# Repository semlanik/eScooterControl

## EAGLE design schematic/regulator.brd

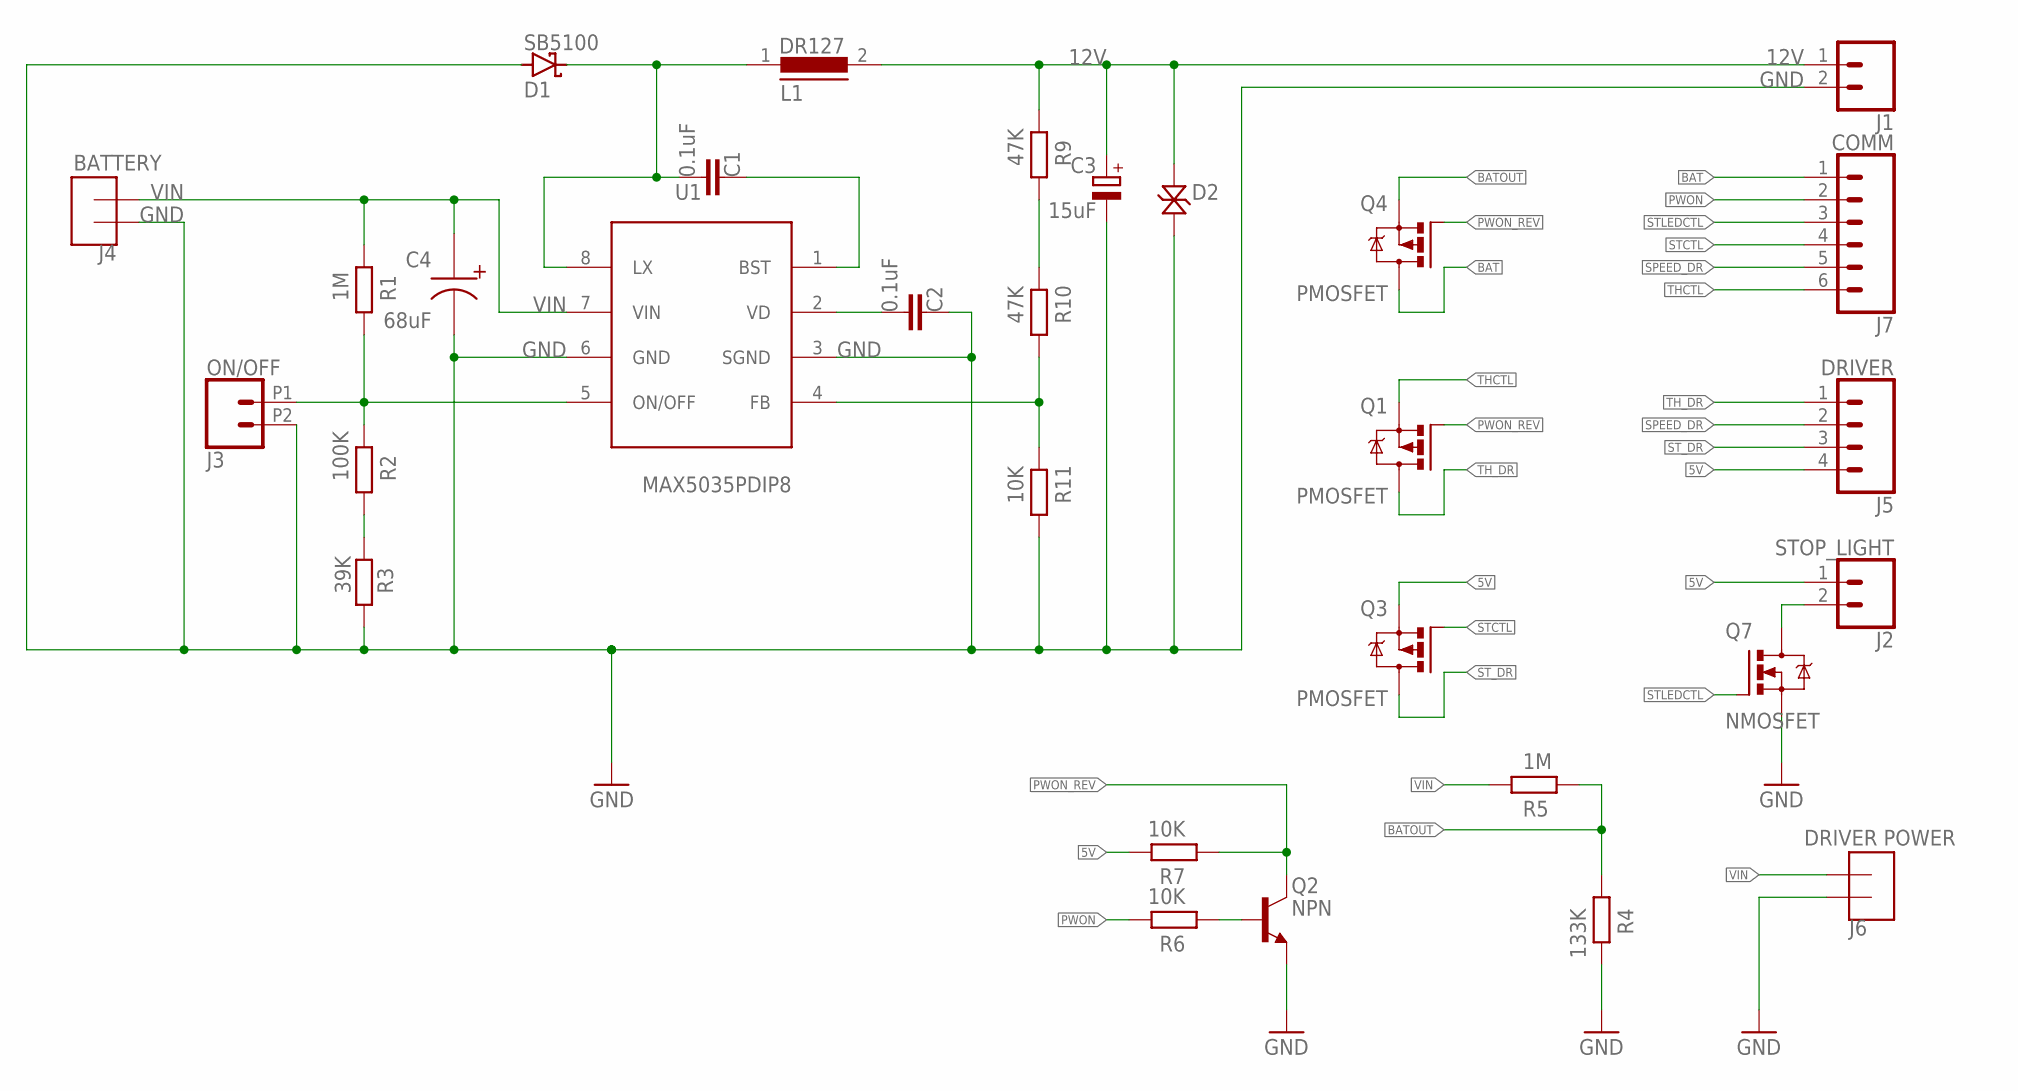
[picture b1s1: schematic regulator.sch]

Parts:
C1, C2: 0.1uF; CAPC3216X135
C3: 15uF; CAPMP7343X310N
C4: 68uF; CAPAE1230X1250N
D1: SB5100; DO201AD
D2: P4SMAJ12CA; DIOM5027X220N
J1: CONN_02PTH3; 1X02_LONGPADS
J2: STOP_LIGHT; 1X02
J3: ON/OFF; 1X02_2.54_SCREWTERM
J4: BATTERY; XT60
J5: DRIVER; 1X04
J6: DRIVER POWER; XT60
J7: COMM; 1X06_LONGPADS
L1: DR127
Q1, Q3, Q4: PMOSFET; SOT23
Q2: NPN; SOT95P237X112-3N
Q7: NMOSFET; SOT23
R1, R5: 1M; R1206
R2: 100K; R1206
R3: 39K; R1206
R4: 133K; R1206
R6, R7, R11: 10K; R1206
R9, R10: 47K; R1206
U1: MAX5035PDIP8; DIP826W56P254L937H458Q8B

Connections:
5V: J2.1, J5.4, Q3.2 (S), R7.1
12V: C3.1 (+), D2.1, J1.1, L1.2, R9.1
BAT: J7.1, Q4.3 (D)
BATOUT: Q4.2 (S), R4.2, R5.1
GND: C2.1, C3.2 (-), C4.2, D1.A, D2.2, J1.2, J3.P2 (2), J4.GND, J6.GND, Q2.1 (E), Q7.2 (S), R3.1, R4.1, R11.2, U1.3 (SGND), U1.6 (GND)
unnamed: C1.1, U1.1 (BST)
unnamed: C1.2, D1.C, L1.1, U1.8 (LX)
unnamed: Q2.2 (B), R6.2
unnamed: C2.2, U1.2 (VD)
unnamed: J3.P1 (1), R1.2, R2.1, U1.5 (ON/OFF)
unnamed: R9.2, R10.1
unnamed: R2.2, R3.2
unnamed: R10.2, R11.1, U1.4 (FB)
PWON: J7.2, R6.1
PWON_REV: Q1.1 (G), Q2.3 (C), Q4.1 (G), R7.2
SPEED_DR: J5.2, J7.5
STCTL: J7.4, Q3.1 (G)
STLEDCTL: J7.3, Q7.1 (G)
STLEDOUT: J2.2, Q7.3 (D)
ST_DR: J5.3, Q3.3 (D)
THCTL: J7.6, Q1.2 (S)
TH_DR: J5.1, Q1.3 (D)
VIN: C4.1, J4.VCC, J6.VCC, R1.1, R5.2, U1.7 (VIN)

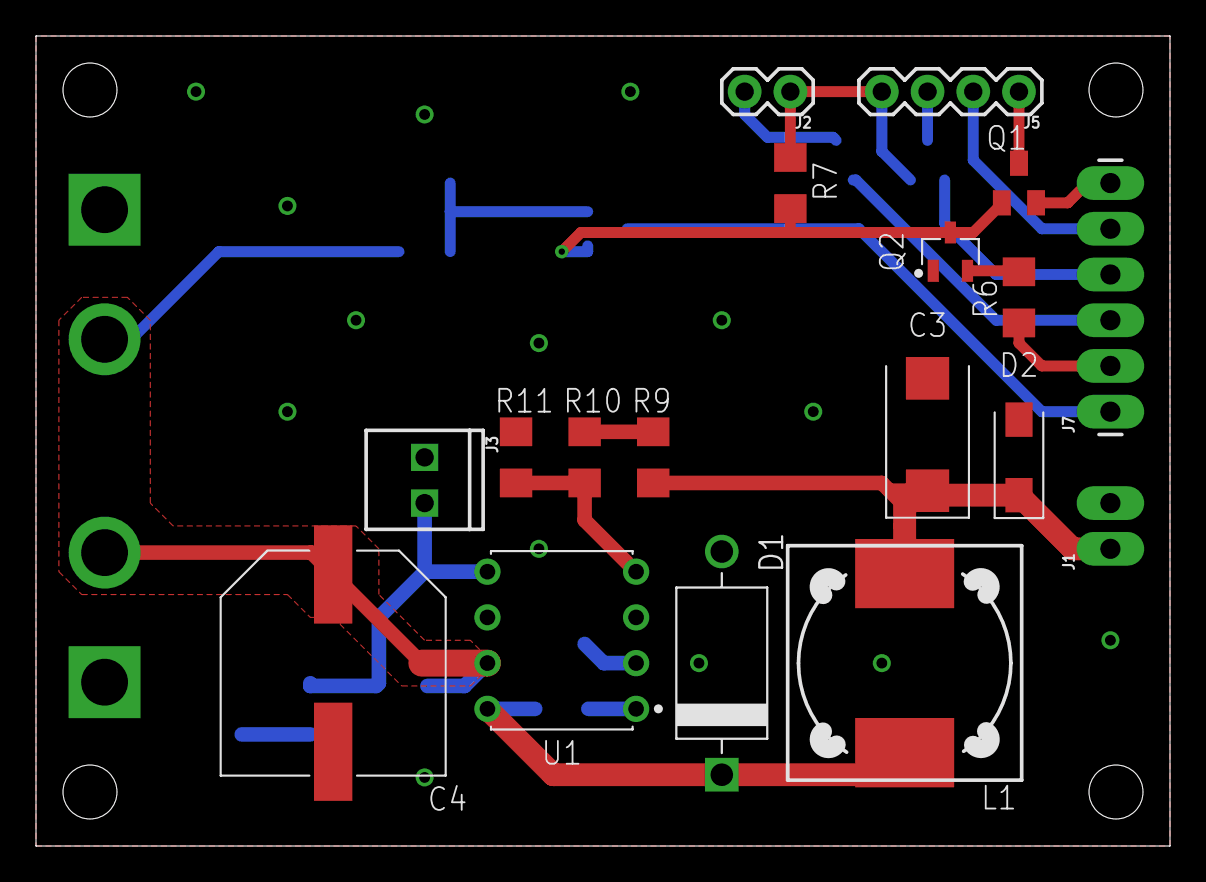
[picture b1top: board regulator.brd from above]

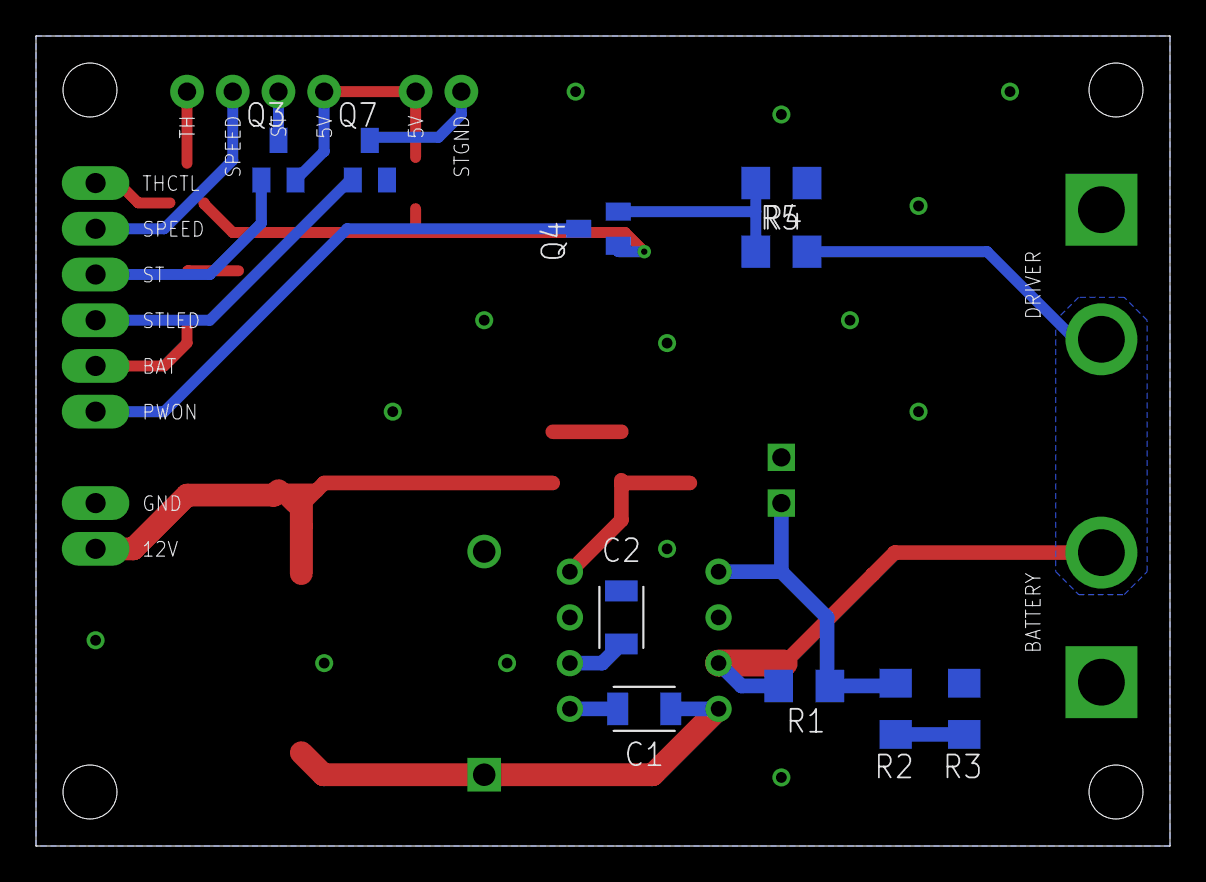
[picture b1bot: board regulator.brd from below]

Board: 2 copper layers, 63.0 x 45.0 mm, 30 parts (10 on the bottom side), 23 nets.

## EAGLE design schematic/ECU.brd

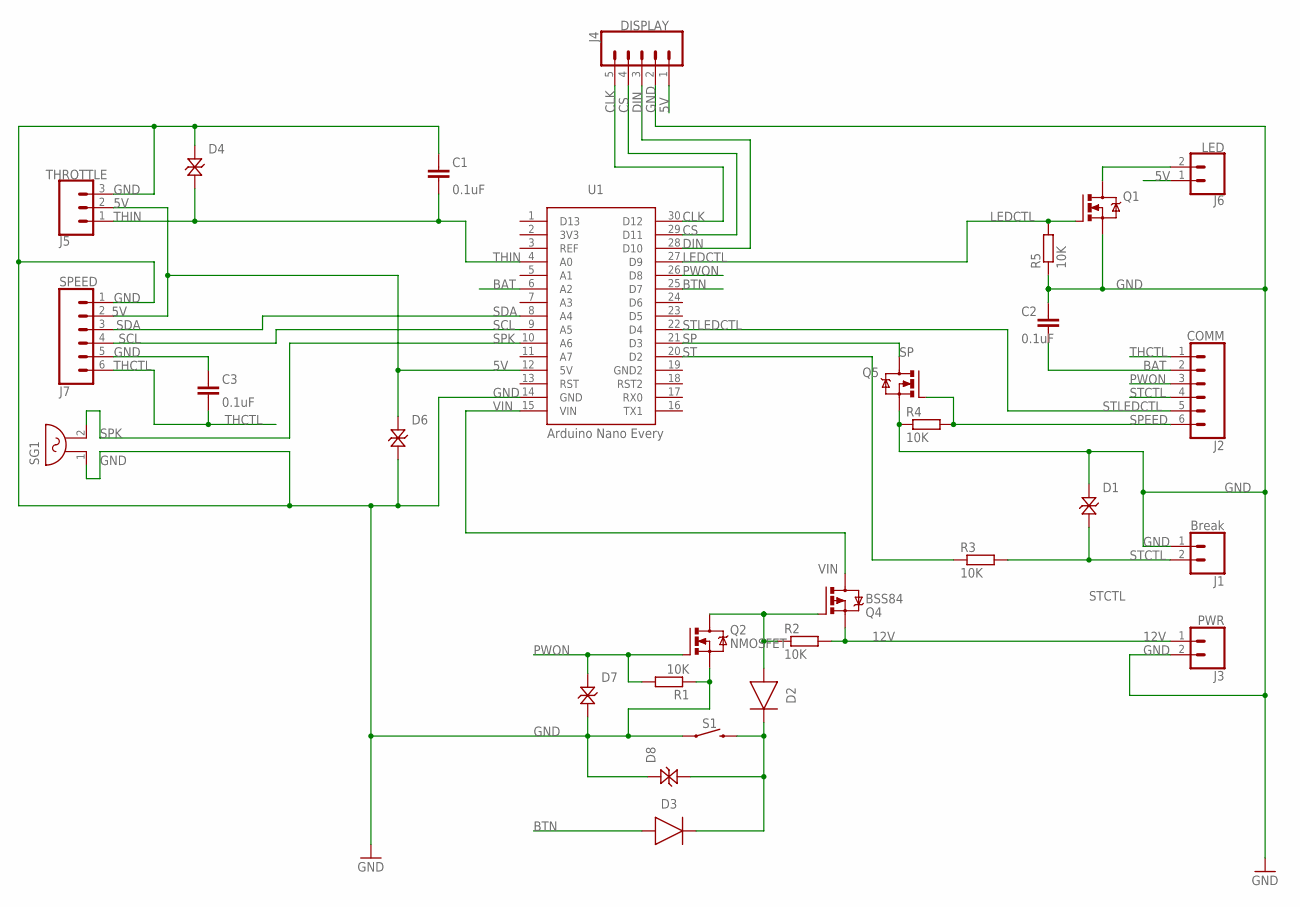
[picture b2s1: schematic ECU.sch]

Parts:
C1, C2, C3: 0.1uF; CAPC3216X135
D1, D4, D6, D7, D8: TVS_DIODESMA; DIOM5027X220N
D2, D3: DIODE_DO-215-AC; SOD6126X290
J1: Break; 1X02
J2: COMM; 1X06
J3: PWR; 1X02
J4: DISPLAY; 1X05
J5: THROTTLE; 1X03
J6: LED; 1X02
J7: SPEED; 1X06
Q1, Q2, Q5: NMOSFET; SOT23
Q4: BSS84; SOT23
R1, R2, R3, R4, R5: 10K; R1206
S1: MOMENTARY-SWITCH-SPST-PTH-6.0MM; TACTILE_SWITCH_PTH_6.0MM
SG1: F/HGP
U1: Arduino Nano Every; SON254P1750X4300X120-30M

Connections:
3V3: U1.2 (3V3)
5V: D6.1, J4.1, J5.2, J6.1, J7.2, U1.12 (5V)
12V: J3.1, Q4.2 (S), R2.2
BAT: C2.1, J2.2, U1.6 (A2)
BTN: D3.2 (A), U1.25 (D7)
CLK: J4.5, U1.30 (D12)
CS: J4.4, U1.29 (D11)
DIN: J4.3, U1.28 (D10)
GND: C1.1, C2.2, C3.2, D1.1, D4.1, D6.2, D7.2, D8.1, J1.1, J3.2, J4.2, J5.3, J7.1, J7.5, Q1.2 (S), Q2.2 (S), Q5.2 (S), R1.1, R4.1, R5.1, S1.1, S1.2 (1), SG1.1, U1.14 (GND)
GND2: U1.19 (GND2)
LEDCTL: Q1.1 (G), R5.2, U1.27 (D9)
unnamed: J6.2, Q1.3 (D)
unnamed: D2.2 (A), Q2.3 (D), Q4.1 (G), R2.1
unnamed: D2.1 (C), D3.1 (C), D8.2, S1.3 (2), S1.4 (2)
PWON: D7.1, J2.3, Q2.1 (G), R1.2, U1.26 (D8)
SCL: J7.4, U1.9 (A5)
SDA: J7.3, U1.8 (A4)
SP: Q5.3 (D), U1.21 (D3)
SPEED: J2.6, Q5.1 (G), R4.2
SPK: SG1.2, U1.10 (A6)
ST: R3.1, U1.20 (D2)
STCTL: D1.2, J1.2, J2.4, R3.2
STLEDCTL: J2.5, U1.22 (D4)
THCTL: C3.1, J2.1, J7.6
THIN: C1.2, D4.2, J5.1, U1.4 (A0)
VIN: Q4.3 (D), U1.15 (VIN)

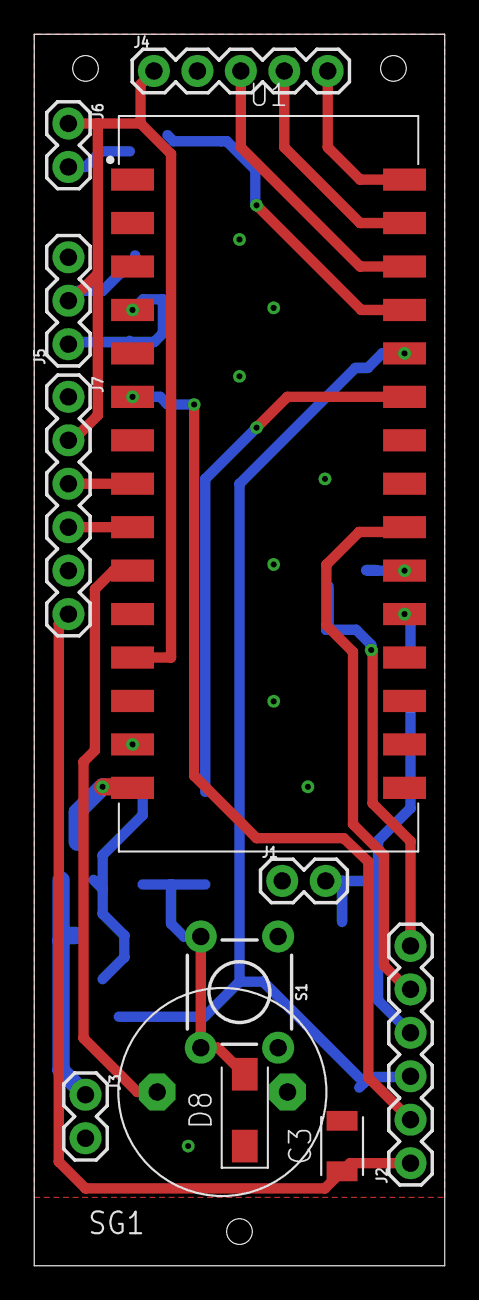
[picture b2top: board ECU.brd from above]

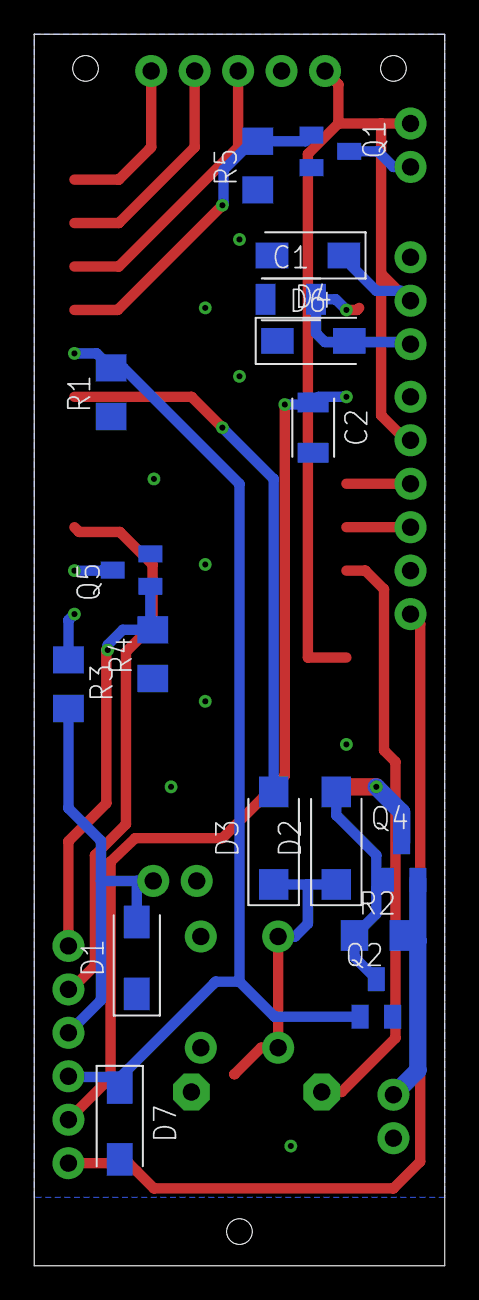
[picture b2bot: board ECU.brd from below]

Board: 2 copper layers, 24.0 x 72.0 mm, 29 parts (17 on the bottom side), 24 nets.

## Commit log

2020-04-02 Inital version
    - Display speed based on hall sensor
    - Display fake battery level
2020-06-09 Implement basic speed control
    - Add speed pedal status read
    - Add cruise control
    - Add break logic
    - Add extra display support and switch speed display position
2020-07-08 Implement speed control
    - Current version of Adafruit MCP4725 library hangs at begin()
    It's either software or hardware issue. Need to migrate to pure
    Wire and check where is issue.
2020-07-09 Migrate to direct wire usage for acceleration control
    - Add initialization delays, to supress intial voltage jumps effect
    for peripheral devices
    - Replace adafruit MCP library with pure Wire. Transmission without
    data at setup() phase breaks application.
2020-07-09 Add acceleration level display
    - Enable second display
    - Add acceleration level display on second display
    - Fix moment speed calculation, add pulse per cicle divider for
    speed pulse sensor.
2020-07-11 Implement button handling
    - Add power button handling
    - Add led switch logic
    - Code cleanup
2020-07-12 Make step-by-step acceleration
    - Make acceleration linear non-jump
    - Move acceleration steps setting to private part
2020-07-13 Code optimization
    - Remove excess millis usage
    - Remove thread dispatch time
    - Replace 'unsigned char' type by 'byte'
    - Optimize drawing
    - Replace 'int' by 'bool' for pin states
    - Align types usage
2020-07-13 Add new display features
    - Optimize display update
    - Add light, eco and stop signs
    - Rework display of battery level
    - Move acceleration level up
2020-07-15 Fix power logic
    - Make default state of PWR pin to 1
    - Change power timings
2020-07-15 Remove useless attachToDisplay
2020-07-17 Add Eagle CAD schematics
    - Add Eagle CAD schematics for regulator and control parts
2020-07-17 Align pin configuration to schematics
2020-07-17 Fix stop sensor schematics
    - Make stop sensor LOW by default, connected to GND.
    - Add control transistor for break on BLDC
2020-07-17 Align stop pin behavior
    - Make stop pin pure input without pullup
    - Inverse stop pin logic, HIGH level is active break
2020-07-17 Fix minor issues in schematics
    - Fix issues with non-connected ground on PCB for speed mosfet
    - Add pdf and gerber files for control unit schematics
2020-07-17 Add regulator schematic pdf
2020-07-18 Update schematics
    - Add TVS diodes for ESD protection
    - Add resistors on MOSFET gates
    - Make voltage divider on 2 resistors(4 previously)
    - Align signal names on regulator and ECU schematics
2020-07-18 Update schematics for regulator
    - Add elements nominals and correct values
    - Fix library inconsistence
    - Few cosmetical changes in schematics
2020-07-18 Replace buzzer with 7.6mm contacts spacing
2020-07-18 Fix minor issues in PCB
2020-07-21 Move regulator elements closer to MAX chip
2020-07-22 Change MAX regulator package
    - Change MAX package to drill-pin
    - Move button to bottom layout
    - Move elements for better work on regulator and ECU
2020-07-25 Rearrange elements in regulator schematics
2020-07-25 eScooter nextgen architecture diagram
2020-07-27 Rework regulator PCB
    - Re-arrange elements
    - Add few ground drills
2020-09-03 Fix regulator schematics
    - Fix regulator schematics, add missed voltage controll resistors
    - Fix deprecated warnings for display
2020-09-11 Add battery level control
2020-09-11 Replace low-side BLDC driver switch by high-side switch
    - Rearrange elements on regulator schematics
2020-10-13 Rework ECU board
    - Align sizes
    - Align elements placement on layers
    - Change power traces in regulator
2020-10-15 Remove high-side switch for driver
    - Keep driver alway on for now
    - Add mosfet switched for speed and throttle
    - Align break work
2020-10-15 Invert stop pin logic according to new schematics
    - Invert stop pin logic to use high-side p-mosfet switch
    - Update TVS diode symbol
2020-10-22 Prettify ECU schematic according to #1
2020-10-26 Cosmetical updates on schematics

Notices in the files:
parts and their libraries:
SparkFun-Connectors: Licensing: Creative Commons ShareAlike 4.0 International - https://creativecommons.org/licenses/by-sa/4.0
